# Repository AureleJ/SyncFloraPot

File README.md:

# 🪴 SyncFloraPot

**SyncFloraPot** is an end-to-end IoT ecosystem designed for smart plant care. It combines custom embedded firmware, a custom KiCad-designed PCB, a time-series backend, and a native Android application to provide real-time monitoring and automated watering.

🔗 **Detailed Project Overview:** [aurelejoblet.com/project/syncflorapot](https://aurelejoblet.com/project/syncflorapot)

---

## 🚀 Overview

SyncFloraPot isn't just a smart pot, it's a complete monitoring solution. It tracks soil moisture, light level, and water reservoir level, allowing users to interact with their plants through a dedicated mobile interface. The onboard OLED screen runs **DianUI**, a custom graphics engine built from scratch for this kind of embedded display.

### Key Features
- **Real-time Data:** Live sensor feedback via MQTT, pushed to the app over WebSockets (Socket.io).
- **Automated Irrigation:** Smart watering logic based on soil moisture thresholds, pump driven through a switching transistor with a hardware safety timer.
- **Local Alerts:** On-device Android notifications (with a per-sensor cooldown) when soil moisture or water level gets too low.
- **BLE Provisioning:** Wi-Fi setup directly from the mobile app, no hardcoded credentials.

---

## 🛠 Technical Stack & Architecture

### 📁 [Firmware](./firmware)
* **Hardware:** ESP32-C3 Microcontroller.
* **Framework:** ESP-IDF, FreeRTOS.
* **Sensors:** Capacitive soil moisture sensor, LDR (light level), ultrasonic sensor (reservoir water level).
* **Communication:** Wi-Fi, MQTT, BLE (Wi-Fi provisioning).
* **Display:** OLED over I2C, driven by DianUI (custom C rendering engine).

### 📁 [Hardware](./hardware)
* **Design:** Custom PCB in KiCad features power supply, sensor interfacing and pump control.

### 📁 [Client](./client)
* **Framework:** Native Android, Kotlin + Jetpack Compose.
* **Features:** Real-time dashboard, local alert notifications, BLE provisioning flow, manual watering override.

### 📁 [Backend](./backend)
* **Environment:** Node.js, Express.
* **Database:** PostgreSQL with the TimescaleDB extension, for time-series sensor history.
* **Communication:** Mosquitto MQTT broker for device-to-cloud messaging, Socket.io for live updates to the app.
* **Auth:** JWT-based user authentication.

---

## 📂 Directory Structure

```txt
SyncFloraPot/
├── firmware/   # ESP32-C3 firmware (ESP-IDF, FreeRTOS)
├── hardware/   # KiCad PCB design 
├── client/     # Native Android app (Kotlin, Jetpack Compose)
└── backend/    # Server, database and MQTT broker setup

```

## 👤 Author

**Aurèle Joblet** - Engineering Student at ESIEA

🌐 [Portfolio](https://aurelejoblet.com) | [LinkedIn](https://www.linkedin.com/in/aurele-joblet/)

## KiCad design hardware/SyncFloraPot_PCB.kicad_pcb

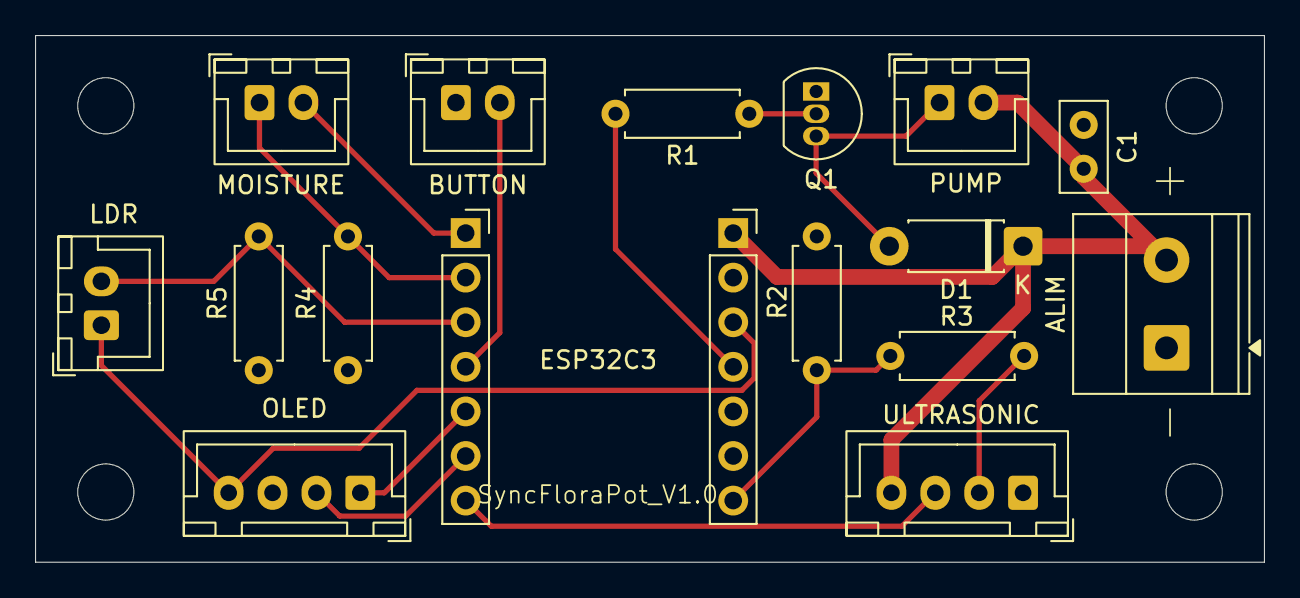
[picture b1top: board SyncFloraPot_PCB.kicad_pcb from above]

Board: 2 copper layers, 70.0 x 30.0 mm, 21 parts (0 on the bottom side), 15 nets.

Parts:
ALIM: Screw_Terminal_01x02; TerminalBlock_Phoenix_MKDS-1,5-2_1x02_P5.00mm_Horizontal
BUTTON: Conn_01x02; JST_XH_B2B-XH-A_1x02_P2.50mm_Vertical
C1: 100nF; C_Disc_D5.0mm_W2.5mm_P2.50mm
D1: D; D_DO-41_SOD81_P7.62mm_Horizontal
H1, H2, H3, H4: MountingHole; MountingHole_3.2mm_M3_ISO7380
J_ESP_L1: Conn_01x07; PinSocket_1x07_P2.54mm_Vertical
J_ESP_R1: Conn_01x07; PinSocket_1x07_P2.54mm_Vertical
LDR: Conn_01x02; JST_XH_B2B-XH-A_1x02_P2.50mm_Vertical
MOISTURE: Conn_01x02; JST_XH_B2B-XH-A_1x02_P2.50mm_Vertical
OLED: Conn_01x04; JST_XH_B4B-XH-A_1x04_P2.50mm_Vertical
PUMP: Conn_01x02; JST_XH_B2B-XH-A_1x02_P2.50mm_Vertical
Q1: Q_NPN_EBC; TO-92_Inline
R1, R2: 1k; R_Axial_DIN0207_L6.3mm_D2.5mm_P7.62mm_Horizontal
R3: 510; R_Axial_DIN0207_L6.3mm_D2.5mm_P7.62mm_Horizontal
R4, R5: 10k; R_Axial_DIN0207_L6.3mm_D2.5mm_P7.62mm_Horizontal
ULTRASONIC: Conn_01x04; JST_XH_B4B-XH-A_1x04_P2.50mm_Vertical

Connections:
+3V3: J_ESP_R1.3, LDR.1, OLED.4
+5V: ALIM.2, C1.1, D1.1 (K), J_ESP_R1.1, PUMP.2, ULTRASONIC.4
GND: ALIM.1, BUTTON.1, C1.2, J_ESP_R1.2, OLED.3, Q1.1 (E), R2.2, R4.1, R5.1, ULTRASONIC.1
unnamed: D1.2 (A), PUMP.1, Q1.3 (C)
unnamed: BUTTON.2, J_ESP_L1.4
unnamed: J_ESP_L1.1, MOISTURE.2
unnamed: J_ESP_L1.2, MOISTURE.1, R4.2
unnamed: J_ESP_L1.3, LDR.2, R5.2
unnamed: J_ESP_L1.5, OLED.1
unnamed: J_ESP_L1.6, OLED.2
unnamed: J_ESP_L1.7, ULTRASONIC.3
unnamed: J_ESP_R1.4, R1.2
unnamed: J_ESP_R1.7, R2.1, R3.2
unnamed: R3.1, ULTRASONIC.2
unnamed: Q1.2 (B), R1.1

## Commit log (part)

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2026-04-12 init
2026-04-12 Add LDR and Moisture sensors gestion with adc manager
2026-04-12 rename
2026-04-12 Passing ADC channels as parameters, improve error gestion
2026-04-12 Adding ultrasonic sensor
2026-04-12 GPIO and ACD types updated in function parameters
2026-04-21 Add I2C manager and OLED display drivers
2026-04-21 Add basic pump driver
2026-04-21 Add WiFi manager
2026-04-21 Add simple UI engine
    Include font, QR and shape rendering
2026-04-21 Add QRCode generator
    MIT-licensed library
2026-04-22 Refactor UI engine and add icons elements
    Add icons elements, and refactor the UI engine to use a centralized element registry with fixed-size pools and have more user-friendly library
2026-04-23 Add animations and icon-in-text
    Introduce element visibility and simple animation support, plus inline icon rendering for text elements
2026-04-23 Add easing equations for animations
2026-04-23 Change lib name
2026-04-23 Refactor UI engine into modular UI
    Replace the monolithic drivers/display UI engine with a modular UI library.
2026-04-24 Rename UI framework in DianUI and add comments
2026-04-25 Add logging and pages
    Introduce a lightweight logging system and add page subsystem.
2026-04-28 Optimise
2026-04-28 Improve LDR ADC reading accuracy
2026-04-28 Improve LDR ADC reading accuracy and add power control pin
2026-04-28 update pins
2026-04-30 Add display contrast control
2026-04-30 Add thread-safe sensor_state
    Introduce a new sensor_state module to hold plant sensor data with thread-safe access. Provides initialization, update functions for light, water, soil, and pump state, plus sensor_state_get_copy() t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
2026-04-30 Add plant_data_t
    Represent plant sensors values and actuators state.
2026-04-30 Add hydration message
    Represents hydration command for pump
2026-04-30 Add monitoring, display, internet, hydration
    Add new service tasks for monitoring, display, internet and hydration. srv_monitoring reads sensors, updates sensor_state, sends watering commands to the hydration queue when soil is low, and notifie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
2026-04-30 Refactor main
2026-04-30 Move project into syncflorapot_firmware directory
2026-04-30 Add backend MQTT + WebSocket server
2026-04-30 Add SyncFloraPot mobile app
2026-04-30 Rename syncflorapot_firmware to firmware
2026-05-11 Revise README with project overview and features
    Expanded project description and added technical details.
2026-05-22 Refactor pots UI
2026-05-22 Improve scan UI and add details
    Scan UI improved
    Details asked to the user like pot name and pot location
2026-05-22 Create fake requests for testing
2026-05-22 Create pot details
    Pot details shows the pot metrics
2026-05-22 Add login page
    Create login page (doesn't work yet)
2026-05-22 Improve UI
2026-05-22 Create Pot Object
2026-05-29 feat: add Docker configuration for backend, database, and MQTT broker
2026-05-29 feat: update server.js to read environment variables for MQTT and port
2026-05-29 chore: add .gitignore for node_modules, env files, and Docker volumes
2026-05-29 chore: add start script
2026-05-30 chore: change timescaledb version and rename "back" container to "api"
2026-05-30 feat: environment variables and health checks
2026-05-30 feat: initial SQL DB setup
2026-05-30 chore: update dependencies in package.json to include dotenv, express, and pg
